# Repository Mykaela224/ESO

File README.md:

# ESO
Senior Design Energy Saving Outlet

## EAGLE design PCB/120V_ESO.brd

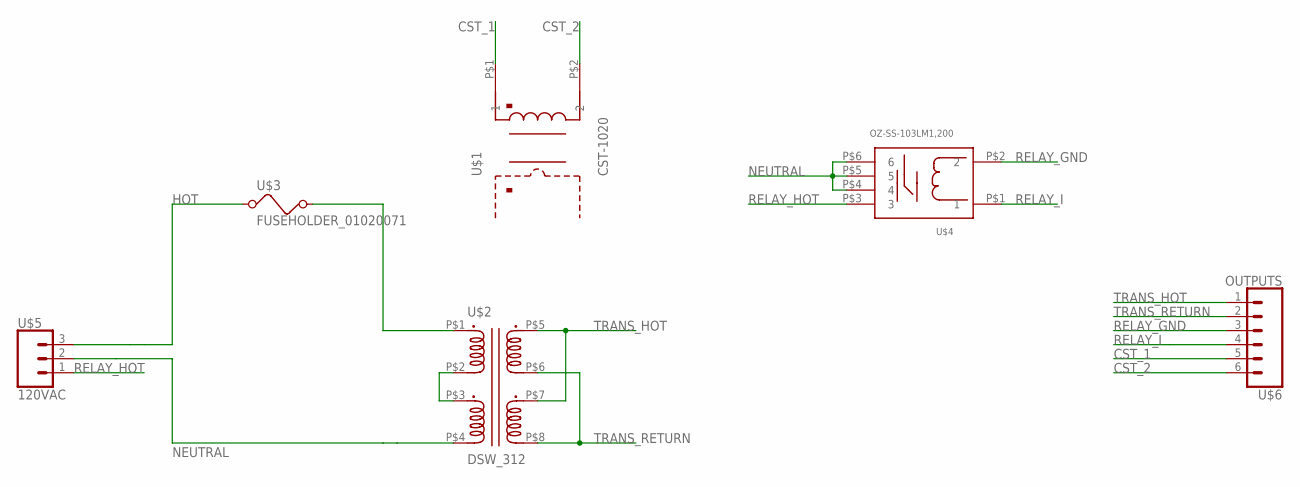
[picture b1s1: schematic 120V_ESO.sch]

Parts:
U$1: CST-1020
U$2: DSW_312
U$3: FUSEHOLDER_01020071; FUSEHOLDER_01020071Z
U$4: OZ-SS-103LM1,200
U$5: 120VAC; 1X03
U$6: OUTPUTS; 1X06

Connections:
CST_1: U$1.P$1 (1), U$6.5
CST_2: U$1.P$2 (2), U$6.6
HOT: U$3.P$1 (1), U$3.P$2 (1), U$5.3
unnamed: U$2.P$1 (P1.1), U$3.P$3 (2), U$3.P$4 (2)
unnamed: U$2.P$2 (P1.2), U$2.P$3 (P2.1)
NEUTRAL: U$2.P$4 (P2.2), U$4.P$4 (4), U$4.P$5 (5), U$4.P$6 (6), U$5.2
RELAY_GND: U$4.P$2 (2), U$6.3
RELAY_HOT: U$4.P$3 (3), U$5.1
RELAY_I: U$4.P$1 (1), U$6.4
TRANS_HOT: U$2.P$5 (S1.1), U$2.P$7 (S2.1), U$6.1
TRANS_RETURN: U$2.P$6 (S1.2), U$2.P$8 (S2.2), U$6.2

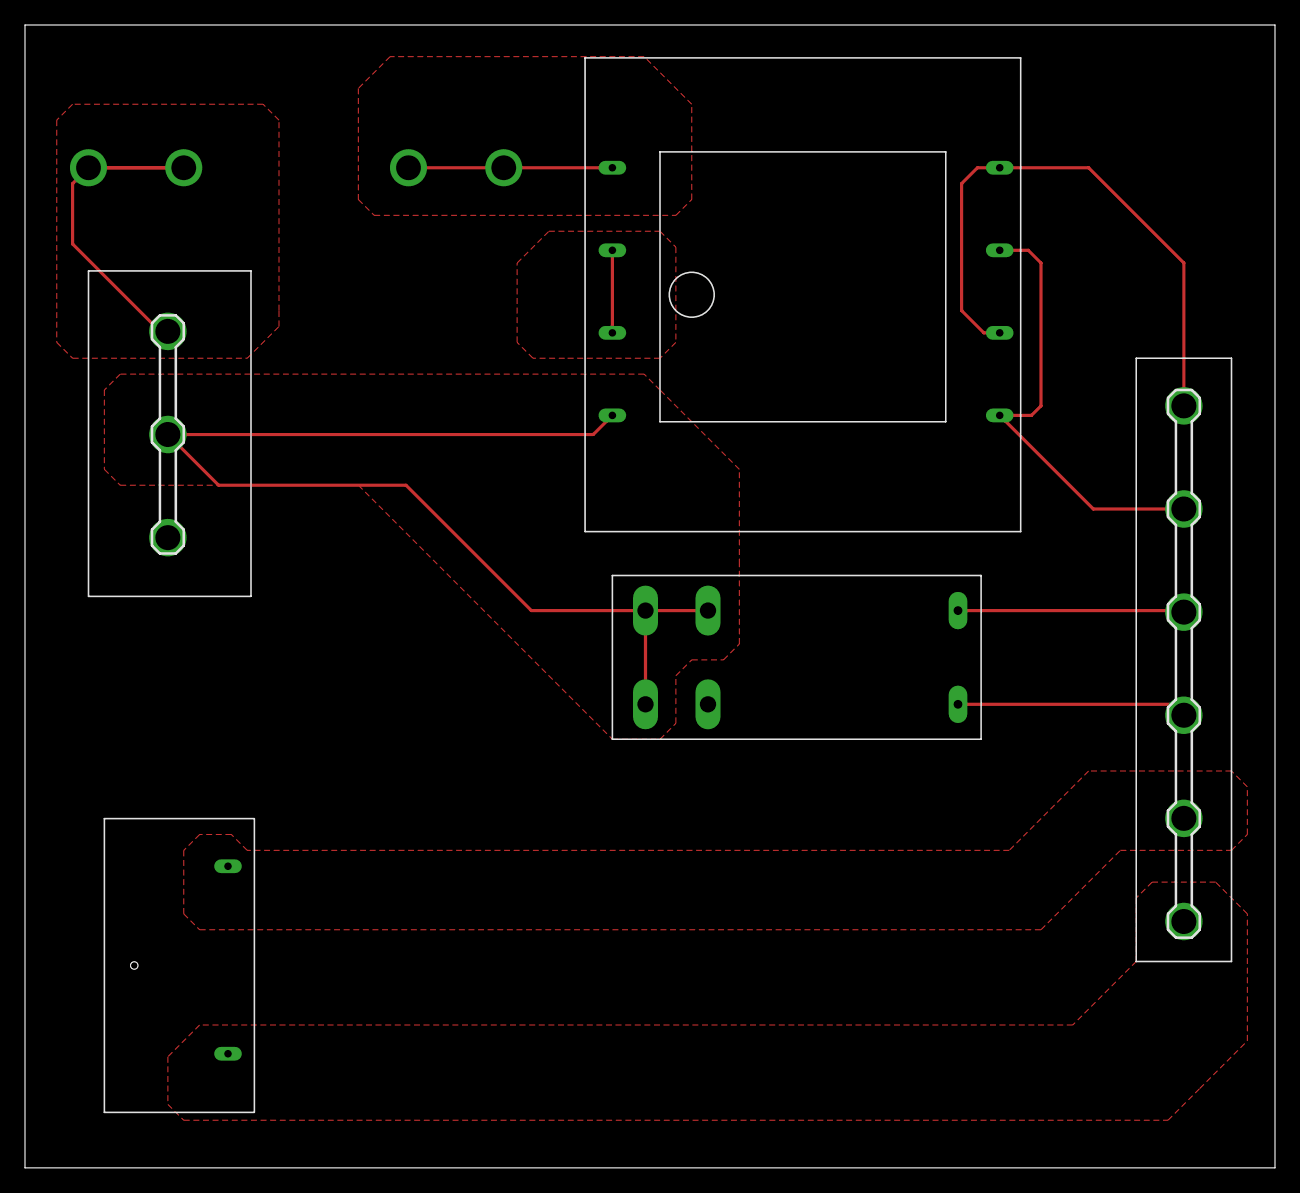
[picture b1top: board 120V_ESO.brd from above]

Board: 2 copper layers, 100.0 x 91.4 mm, 6 parts (0 on the bottom side), 11 nets.

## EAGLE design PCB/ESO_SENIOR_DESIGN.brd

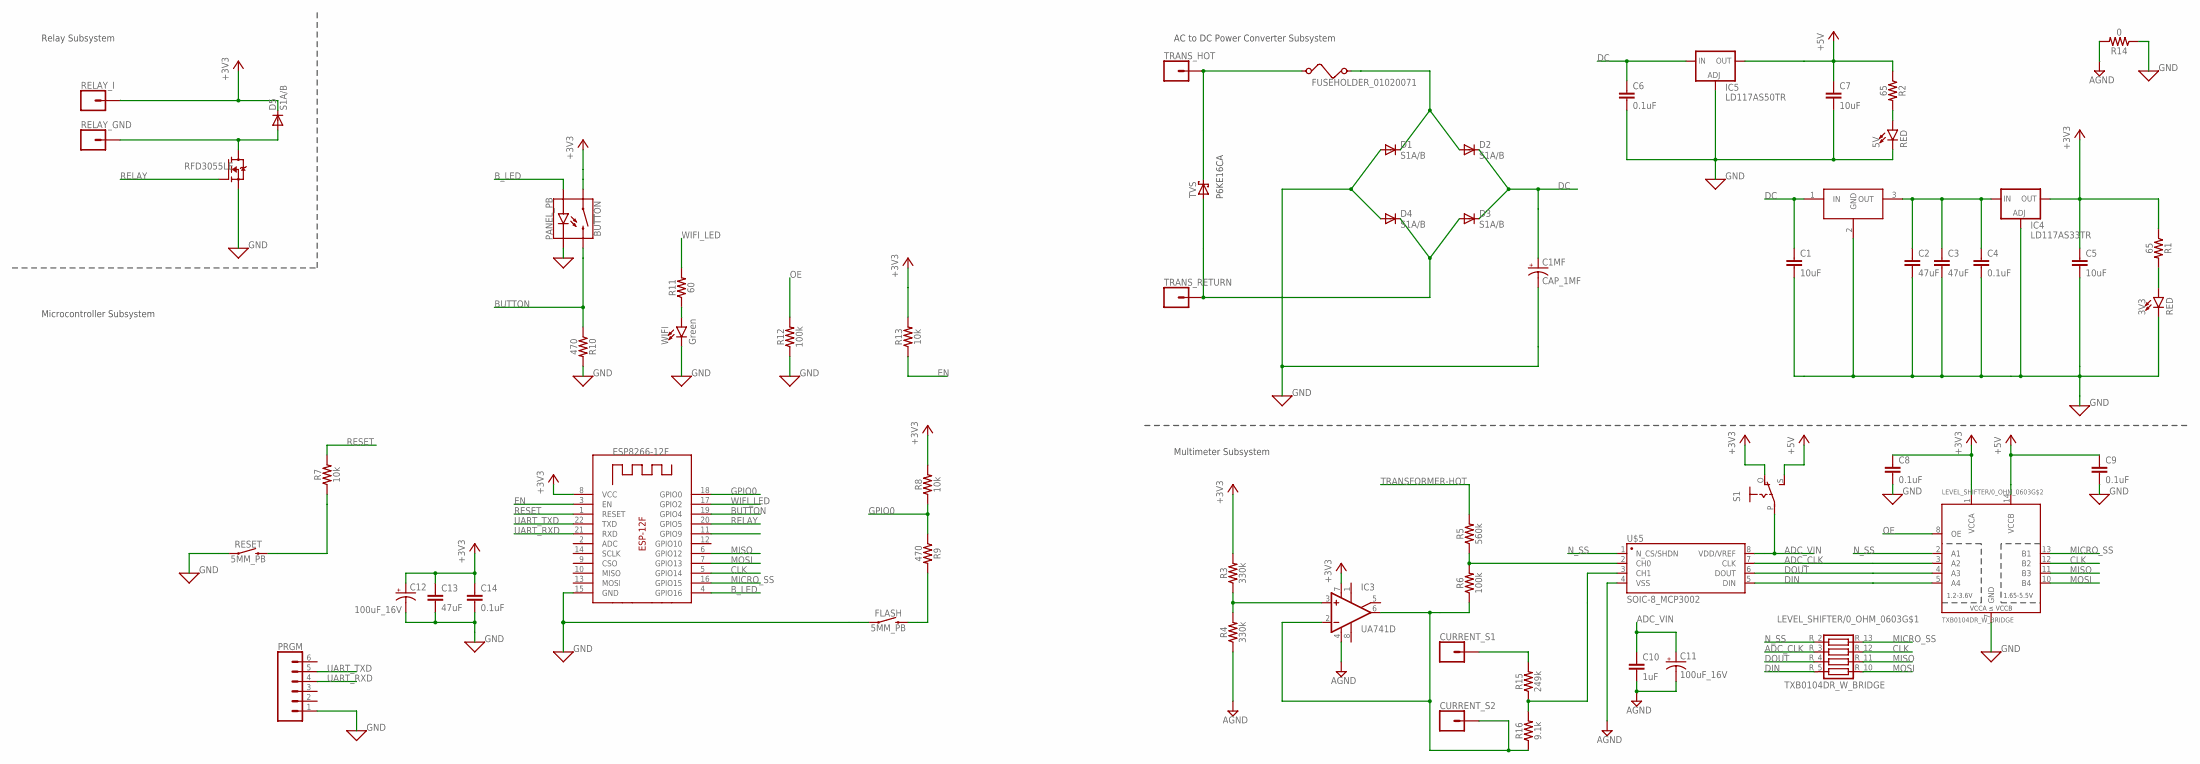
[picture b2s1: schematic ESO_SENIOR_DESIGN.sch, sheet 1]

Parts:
3V3, 5V: RED; LED-1206
12F: ESP-12F
BUTTON: PANEL_PB
C1, C5, C7: 10uF; C0805
C1MF: CAP_1MF; PANASONIC_H13
C2, C3, C13: 47uF; C0805
C4, C6, C8, C9, C14: 0.1uF; C0805
C10: 1uF; C0805
C11, C12: 100uF_16V; PANASONIC_C
CURRENT_S1, CURRENT_S2: CONN_01; 1X01
D1, D2, D3, D4, D5: S1A/B; SMB
FLASH: 5MM_PB; TACTILE_SWITCH_SMD_5MM
IC3: UA741D; SO08
IC4: LD117AS33TR; SOT223
IC5: LD117AS50TR; SOT223
LEVEL_SHIFTER/0_OHM_0603: TXB0104DR_W_BRIDGE; SO14
PRGM: CONN_06NO_SILK_FEMALE_PTH; 1X06_NO_SILK
Q$1: RFD3055LE; TO92-SGD
R1, R2: 65; 0805
R3, R4: 330k; 0805
R5: 560k; 0805
R6, R12: 100k; 0805
R7, R8, R13: 10k; 0805
R9, R10: 470; 0805
R11: 60; 0805
R14: 0; 0805
R15: 249k; 0805
R16: 9.1k; 0805
RELAY_GND: CONN_01; 1X01
RELAY_I: CONN_01; 1X01
RESET: 5MM_PB; TACTILE_SWITCH_SMD_5MM
S1: EG1218S; EG1218
TRANS_HOT: CONN_01; 1X01
TRANS_RETURN: CONN_01; 1X01
TVS: 1N5819-T; DO41-7.6
U$1: FUSEHOLDER_01020071; FUSEHOLDER_01020071Z
U$3: BUCK; TO220H
U$5: SOIC-8_MCP3002; SO08-0.15
WIFI: Green; LED-1206

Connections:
+3V3: 12F.8 (VCC), BUTTON.1, C5.1, C8.1, C12.+, C13.1, C14.1, D5.C, IC3.7 (V+), IC4.2 (OUT), IC4.4 (OUT), LEVEL_SHIFTER/0_OHM_0603.1 (VCCA), R1.1, R3.2, R8.2, R13.2, RELAY_I.1, S1.O
+5V: C7.1, C9.1, IC5.2 (OUT), IC5.4 (OUT), LEVEL_SHIFTER/0_OHM_0603.14 (VCCB), R2.1, S1.S
ADC_CLK: LEVEL_SHIFTER/0_OHM_0603.3 (A2), LEVEL_SHIFTER/0_OHM_0603.R_3 (2), U$5.7 (CLK)
ADC_VIN: C10.1, C11.+, S1.P, U$5.8 (VDD/VREF)
AGND: C10.2, C11.-, IC3.4 (V-), R4.1, R14.2, U$5.4 (VSS)
BUTTON: 12F.19 (GPIO4), BUTTON.2, R10.1
B_LED: 12F.4 (GPIO16), BUTTON.3 (A)
C2: C2.1, C3.1, C4.1, IC4.3 (IN), U$3.3 (OUT)
CLK: 12F.5 (GPIO14), LEVEL_SHIFTER/0_OHM_0603.12 (B2), LEVEL_SHIFTER/0_OHM_0603.R_12 (7)
DC: C1.1, C1MF.+, C6.1, D2.C, D3.C, IC5.3 (IN), U$3.1 (IN)
DIN: LEVEL_SHIFTER/0_OHM_0603.5 (A4), LEVEL_SHIFTER/0_OHM_0603.R_5 (4), U$5.5 (DIN)
DOUT: LEVEL_SHIFTER/0_OHM_0603.4 (A3), LEVEL_SHIFTER/0_OHM_0603.R_4 (3), U$5.6 (DOUT)
EN: 12F.3 (EN), R13.1
GND: 3V3.C, 5V.C, 12F.15 (GND), BUTTON.4 (C), C1.2, C1MF.-, C2.2, C3.2, C4.2, C5.2, C6.2, C7.2, C8.2, C9.2, C12.-, C13.2, C14.2, D1.A, D4.A, FLASH.1, FLASH.3 (1), IC4.1 (ADJ), IC5.1 (ADJ), LEVEL_SHIFTER/0_OHM_0603.7 (GND), PRGM.1, Q$1.S, R10.2, R12.1, R14.1, RESET.1, RESET.3 (1), U$3.2 (GND), WIFI.C
GPIO0: 12F.18 (GPIO0), R8.1, R9.1
MICRO_SS: 12F.16 (GPIO15), LEVEL_SHIFTER/0_OHM_0603.13 (B1), LEVEL_SHIFTER/0_OHM_0603.R_13 (8)
MISO: 12F.6 (GPIO12), LEVEL_SHIFTER/0_OHM_0603.11 (B3), LEVEL_SHIFTER/0_OHM_0603.R_11 (6)
MOSI: 12F.7 (GPIO13), LEVEL_SHIFTER/0_OHM_0603.10 (B4), LEVEL_SHIFTER/0_OHM_0603.R_10 (5)
unnamed: R7.1, RESET.2, RESET.4 (2)
unnamed: D1.C, D2.A, U$1.P$3 (2)
unnamed: 3V3.A, R1.2
unnamed: IC3.3 (+IN), R3.1, R4.2
unnamed: R15.1, R16.2, U$5.3 (CH1)
unnamed: R5.1, R6.2, U$5.2 (CH0)
unnamed: 5V.A, R2.2
unnamed: CURRENT_S2.1, IC3.2 (-IN), IC3.6 (OUT), R6.1, R16.1
unnamed: FLASH.2, FLASH.4 (2), R9.2
unnamed: R11.1, WIFI.A
unnamed: D5.A, Q$1.D, RELAY_GND.1
unnamed: CURRENT_S1.1, R15.2
N_SS: LEVEL_SHIFTER/0_OHM_0603.2 (A1), LEVEL_SHIFTER/0_OHM_0603.R_2 (1), U$5.1 (N_CS/SHDN)
OE: 12F.11 (GPIO9), LEVEL_SHIFTER/0_OHM_0603.8 (OE), R12.2
RELAY: 12F.20 (GPIO5), Q$1.G
RESET: 12F.1 (RESET), R7.2
TRANSFORMER-HOT: R5.2, TRANS_HOT.1, TVS.C, U$1.P$1 (1)
TRANSFORMER-RETURN: D3.A, D4.C, TRANS_RETURN.1, TVS.A
UART_RXD: 12F.21 (RXD), PRGM.4
UART_TXD: 12F.22 (TXD), PRGM.5
WIFI_LED: 12F.17 (GPIO2), R11.2

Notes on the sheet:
ESP8266-12F
AC to DC Power Converter Subsystem
Multimeter Subsystem
Relay Subsystem
Microcontroller Subsystem
P6KE16CA

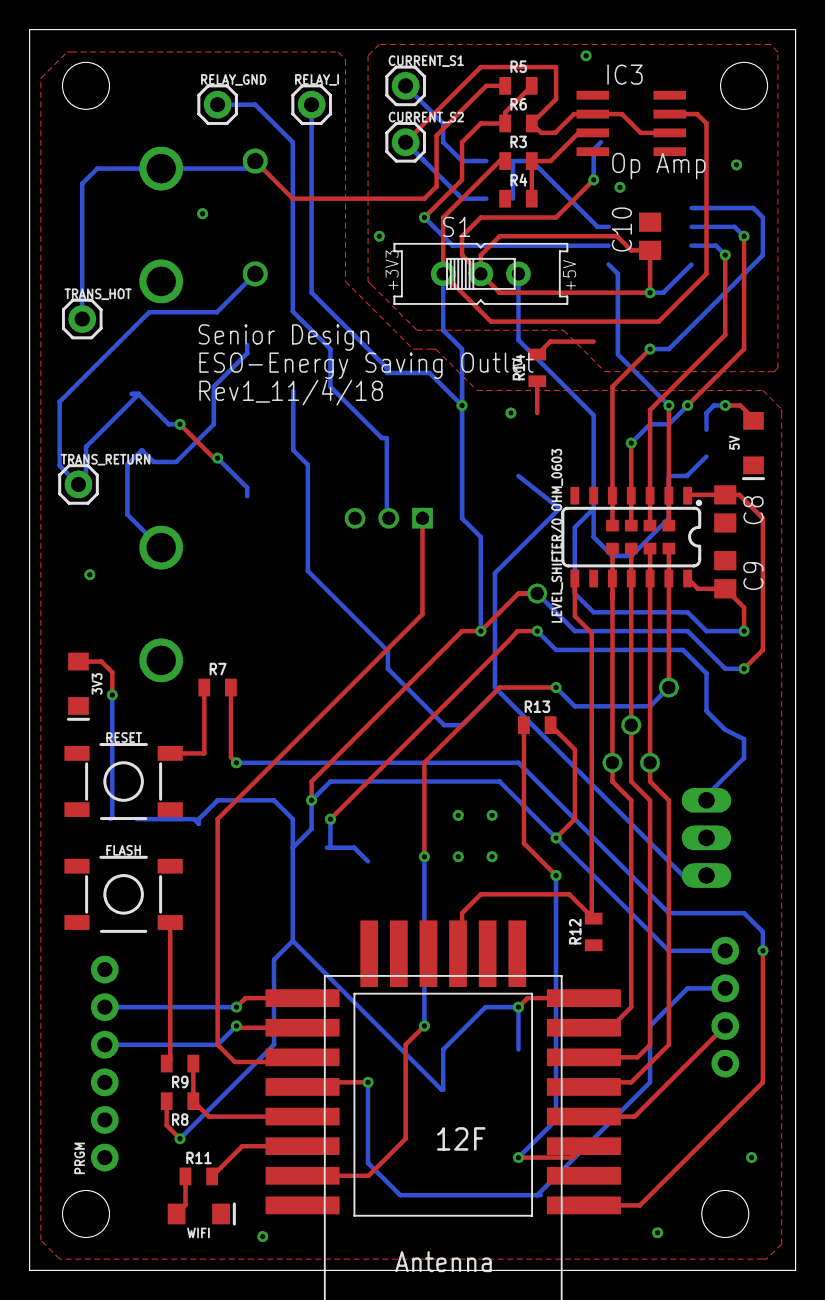
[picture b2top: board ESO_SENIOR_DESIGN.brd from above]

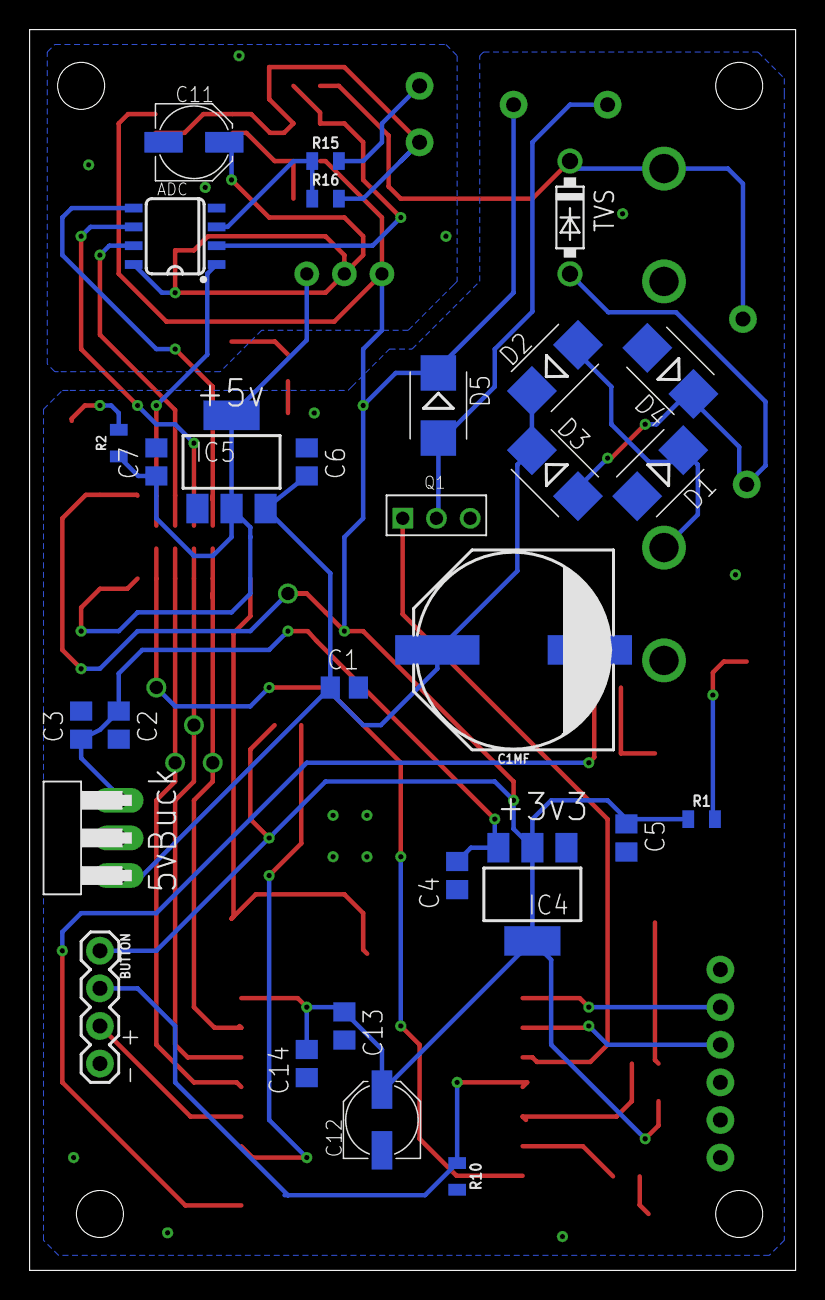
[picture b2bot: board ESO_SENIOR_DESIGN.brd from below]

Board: 2 copper layers, 51.7 x 83.8 mm, 60 parts (29 on the bottom side), 39 nets.

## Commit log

2018-11-09 added Purpose of Software folder

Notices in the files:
parts and their libraries:
SparkFun-LED: Licensing: Creative Commons ShareAlike 4.0 International - https://creativecommons.org/licenses/by-sa/4.0
